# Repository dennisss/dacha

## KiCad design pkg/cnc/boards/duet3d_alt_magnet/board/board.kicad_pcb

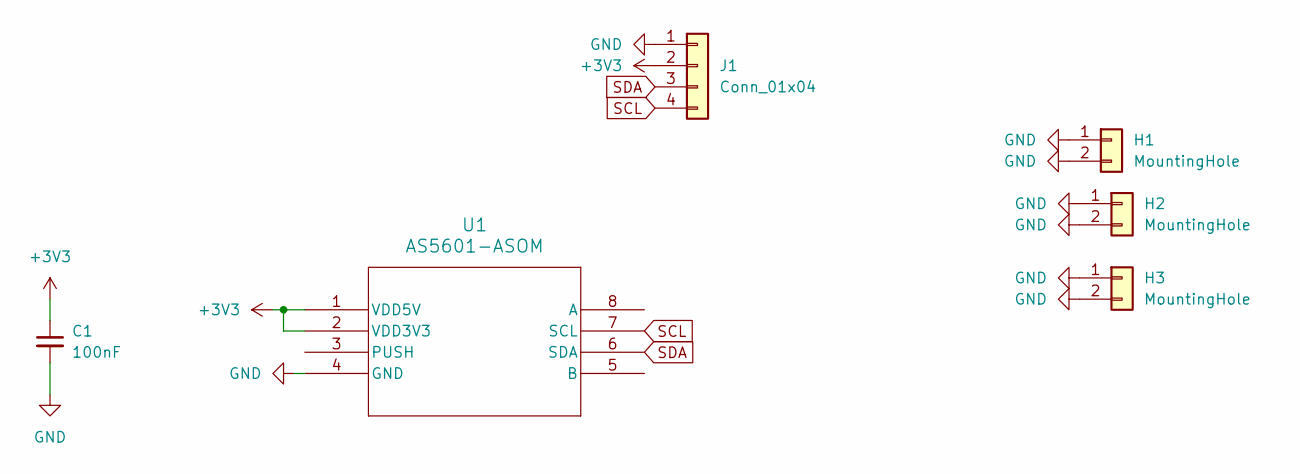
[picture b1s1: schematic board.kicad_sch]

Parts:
C1: 100nF; C_0805_2012Metric_Pad1.18x1.45mm_HandSolder
H1, H2, H3: MountingHole; M2-5-NPTH
J1: Conn_01x04; JST_SH_SM04B-SRSS-TB_1x04-1MP_P1.00mm_Horizontal
U1: AS5601-ASOM; SOIC8_AMS-M

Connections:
+3V3: C1.1, J1.2, U1.1 (VDD5V), U1.2 (VDD3V3)
GND: C1.2, H1.1, H1.2, H2.1, H2.2, H3.1, H3.2, J1.1, U1.4 (GND)
SCL: J1.4, U1.7 (SCL)
SDA: J1.3, U1.6 (SDA)

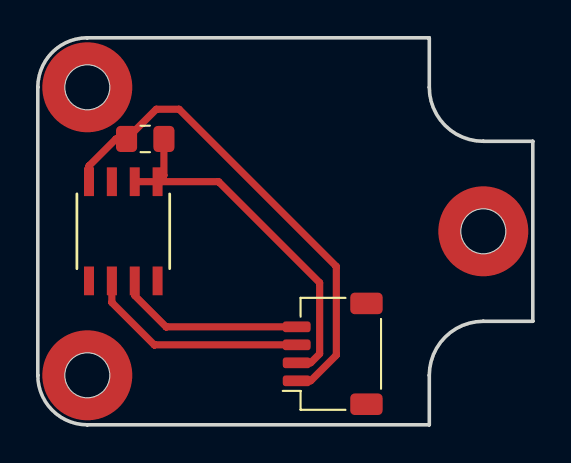
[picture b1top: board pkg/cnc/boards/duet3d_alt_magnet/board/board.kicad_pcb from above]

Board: 2 copper layers, 27.5 x 21.5 mm, 6 parts (0 on the bottom side), 4 nets.

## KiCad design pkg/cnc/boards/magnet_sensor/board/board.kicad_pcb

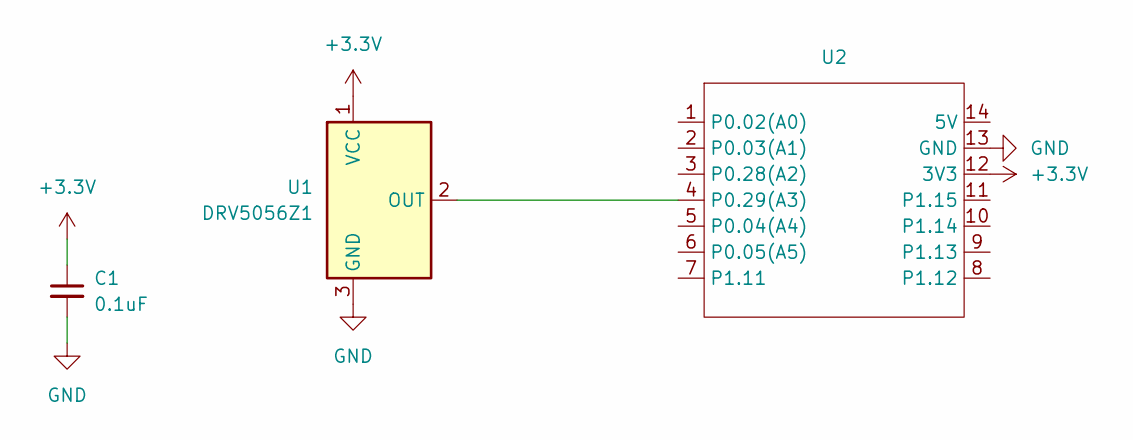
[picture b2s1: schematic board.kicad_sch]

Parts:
C1: 0.1uF; C_0805_2012Metric_Pad1.18x1.45mm_HandSolder
U1: DRV5056Z1; SOT-23
U2: XIAO_NRF52840

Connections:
+3.3V: C1.1, U1.1 (VCC), U2.12 (3V3)
GND: C1.2, U1.3 (GND), U2.13 (GND)
unnamed: U1.2 (OUT), U2.4 (P0.29(A3))

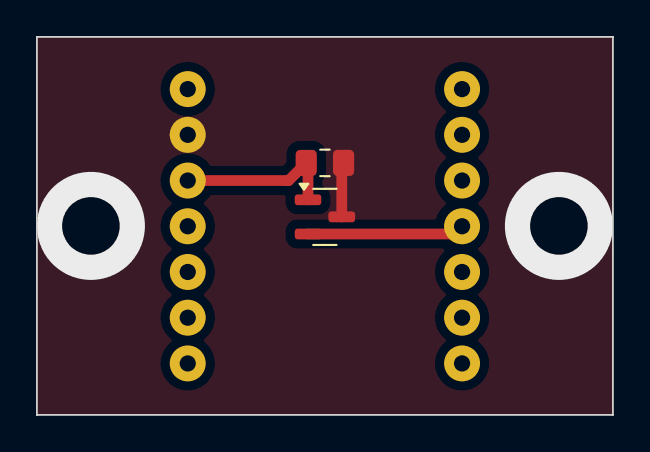
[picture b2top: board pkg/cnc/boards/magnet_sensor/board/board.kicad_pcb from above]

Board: 2 copper layers, 32.0 x 21.0 mm, 3 parts (1 on the bottom side), 3 nets.

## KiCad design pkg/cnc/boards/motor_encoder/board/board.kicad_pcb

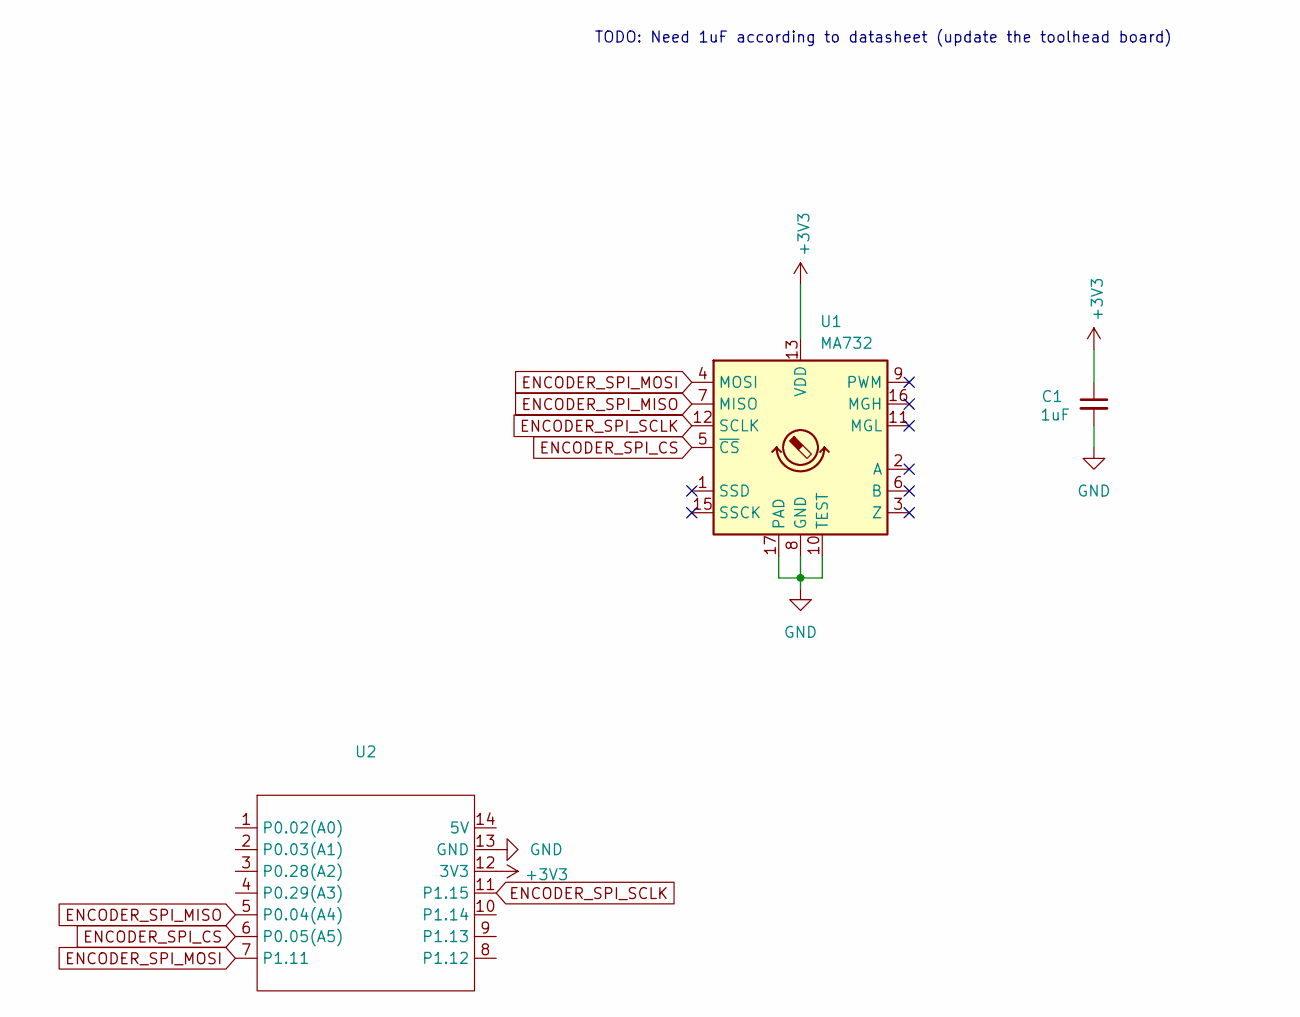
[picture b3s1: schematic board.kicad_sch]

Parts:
C1: 1uF; C_0603_1608Metric_Pad1.08x0.95mm_HandSolder
U1: MA732; QFN-16-1EP_3x3mm_P0.5mm_EP1.75x1.75mm
U2: XIAO_NRF52840

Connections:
+3V3: C1.1, U1.13 (VDD), U2.12 (3V3)
ENCODER_SPI_CS: U1.5 (~CS), U2.6 (P0.05(A5))
ENCODER_SPI_MISO: U1.7 (MISO), U2.5 (P0.04(A4))
ENCODER_SPI_MOSI: U1.4 (MOSI), U2.7 (P1.11)
ENCODER_SPI_SCLK: U1.12 (SCLK), U2.11 (P1.15)
GND: C1.2, U1.8 (GND), U1.10 (TEST), U1.17 (PAD), U2.13 (GND)

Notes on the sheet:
TODO: Need 1uF according to datasheet (update the toolhead board)

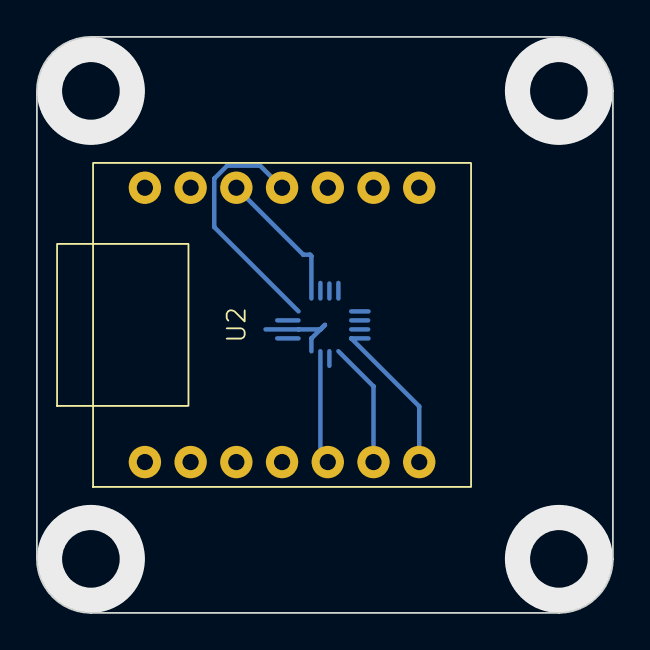
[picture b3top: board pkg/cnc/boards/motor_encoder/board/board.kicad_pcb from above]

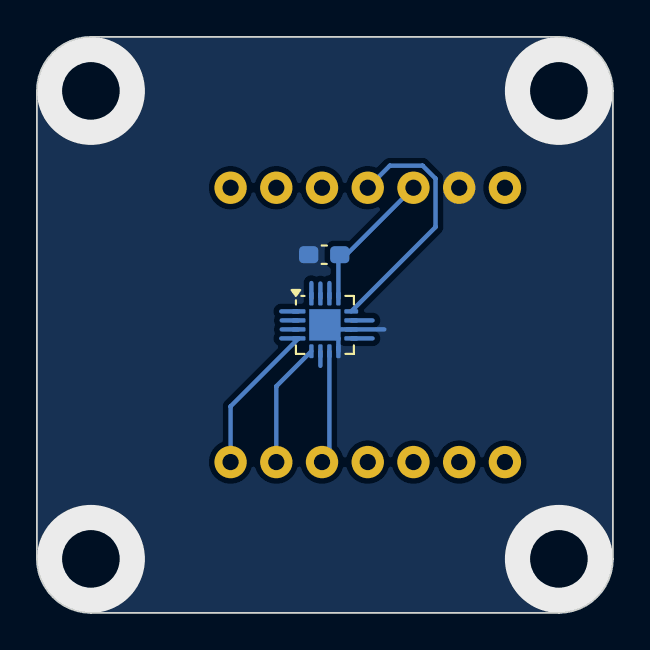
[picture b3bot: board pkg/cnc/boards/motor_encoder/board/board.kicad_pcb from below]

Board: 2 copper layers, 32.0 x 32.0 mm, 3 parts (2 on the bottom side), 6 nets.

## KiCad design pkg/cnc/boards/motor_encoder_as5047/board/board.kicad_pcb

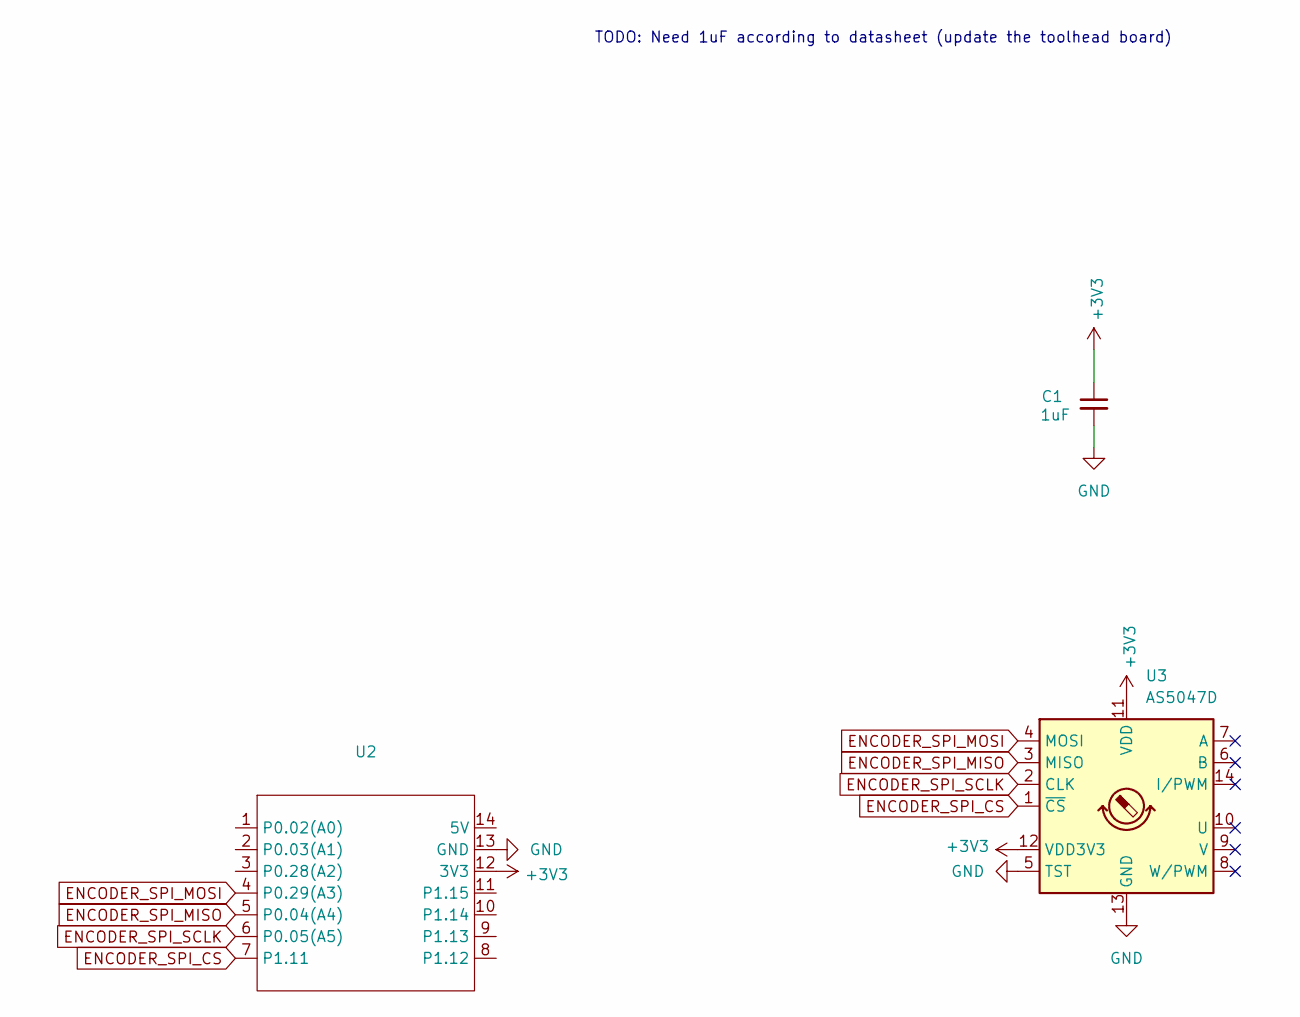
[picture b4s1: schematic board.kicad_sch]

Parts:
C1: 1uF; C_0603_1608Metric_Pad1.08x0.95mm_HandSolder
U2: XIAO_NRF52840
U3: AS5047D; TSSOP-14_4.4x5mm_P0.65mm

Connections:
+3V3: C1.1, U2.12 (3V3), U3.11 (VDD), U3.12 (VDD3V3)
ENCODER_SPI_CS: U2.7 (P1.11), U3.1 (~CS)
ENCODER_SPI_MISO: U2.5 (P0.04(A4)), U3.3 (MISO)
ENCODER_SPI_MOSI: U2.4 (P0.29(A3)), U3.4 (MOSI)
ENCODER_SPI_SCLK: U2.6 (P0.05(A5)), U3.2 (CLK)
GND: C1.2, U2.13 (GND), U3.5 (TST), U3.13 (GND)

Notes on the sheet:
TODO: Need 1uF according to datasheet (update the toolhead board)

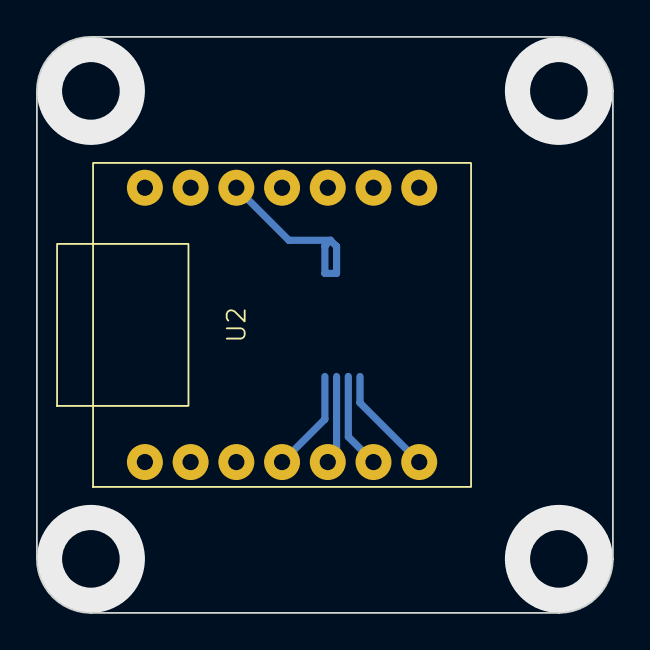
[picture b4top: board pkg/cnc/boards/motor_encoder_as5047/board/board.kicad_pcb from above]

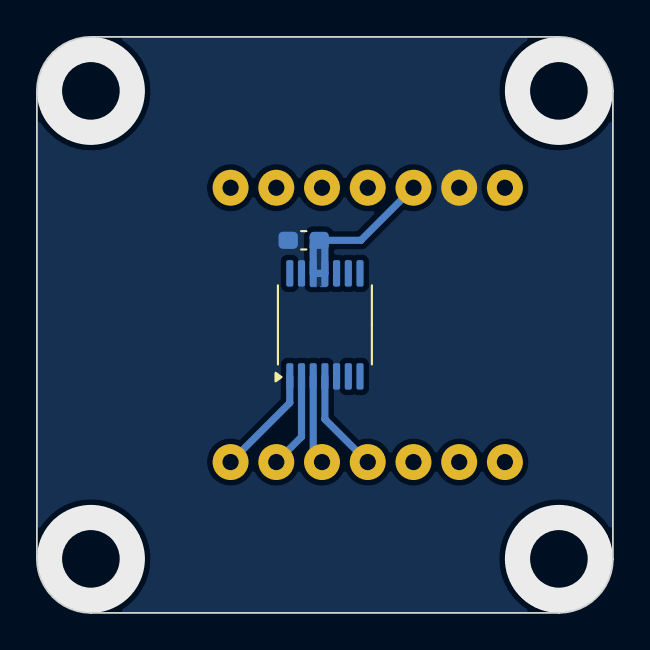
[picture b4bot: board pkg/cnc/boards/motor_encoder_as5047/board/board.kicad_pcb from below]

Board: 2 copper layers, 32.0 x 32.0 mm, 3 parts (2 on the bottom side), 6 nets.

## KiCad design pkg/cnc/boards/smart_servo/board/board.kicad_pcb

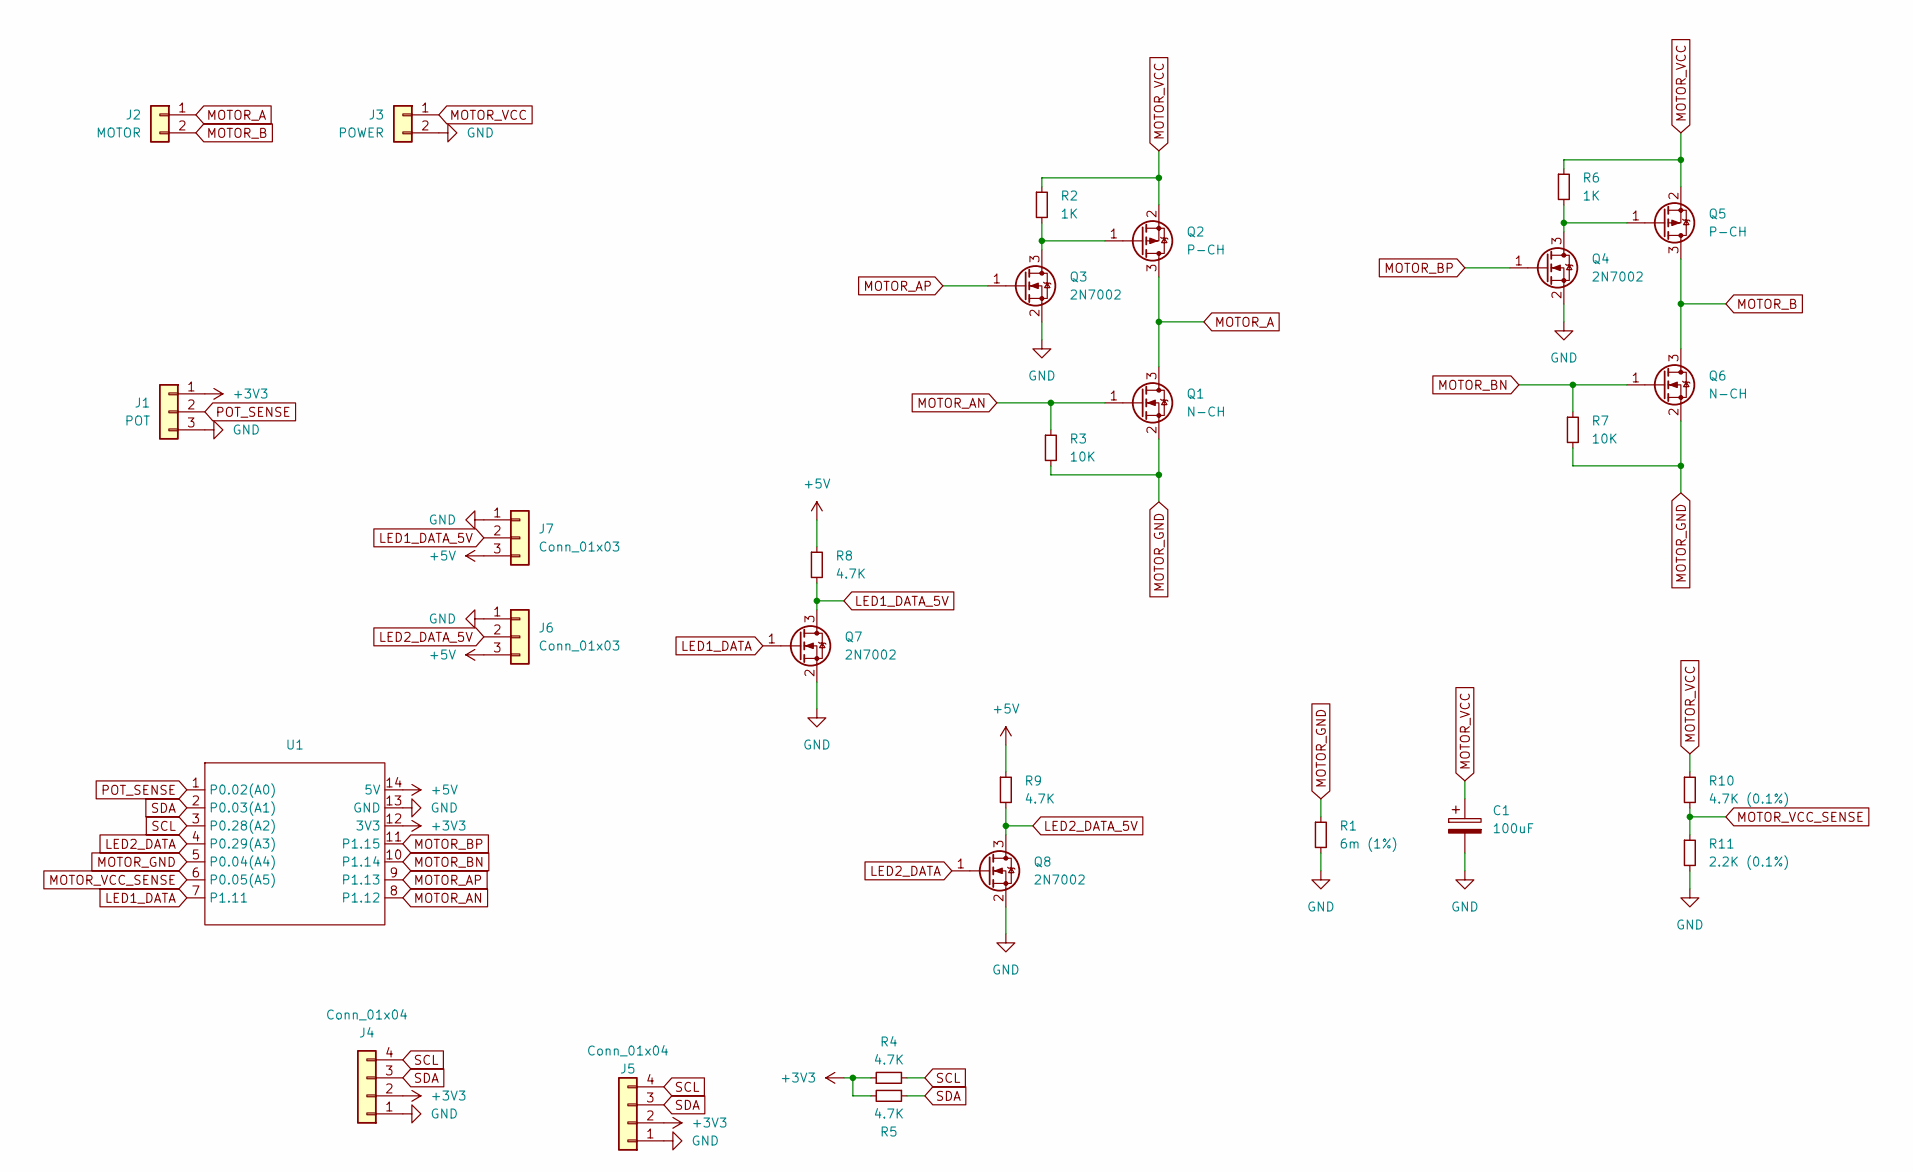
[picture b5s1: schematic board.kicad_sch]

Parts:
C1: 100uF; CP_Elec_6.3x7.7
J1: POT; JST_PH_S3B-PH-K_1x03_P2.00mm_Horizontal
J2: MOTOR; JST_XH_S2B-XH-A_1x02_P2.50mm_Horizontal
J3: POWER; Molex_Micro-Fit_3.0_43650-0210_1x02-1MP_P3.00mm_Horizontal
J4, J5: Conn_01x04; JST_SH_SM04B-SRSS-TB_1x04-1MP_P1.00mm_Horizontal
J6, J7: Conn_01x03; JST_PH_S3B-PH-K_1x03_P2.00mm_Horizontal
Q1, Q6: N-CH; SOT-23
Q2, Q5: P-CH; SOT-23
Q3, Q4, Q7, Q8: 2N7002; SOT-23
R1: 6m (1%); R_0805_2012Metric_Pad1.20x1.40mm_HandSolder
R2, R6: 1K; R_0603_1608Metric_Pad0.98x0.95mm_HandSolder
R3, R7: 10K; R_0603_1608Metric_Pad0.98x0.95mm_HandSolder
R4, R5, R8, R9: 4.7K; R_0603_1608Metric_Pad0.98x0.95mm_HandSolder
R10: 4.7K (0.1%); R_0603_1608Metric_Pad0.98x0.95mm_HandSolder
R11: 2.2K (0.1%); R_0603_1608Metric_Pad0.98x0.95mm_HandSolder
U1: XIAO_NRF52840

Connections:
+3V3: J1.1, J4.2, J5.2, R4.1, R5.2, U1.12 (3V3)
+5V: J6.3, J7.3, R8.1, R9.1, U1.14 (5V)
GND: C1.2, J1.3, J3.2, J3.MP, J4.1, J5.1, J6.1, J7.1, Q3.2 (S), Q4.2 (S), Q7.2 (S), Q8.2 (S), R1.2, R11.2, U1.13 (GND)
LED1_DATA: Q7.1 (G), U1.7 (P1.11)
LED1_DATA_5V: J7.2, Q7.3 (D), R8.2
LED2_DATA: Q8.1 (G), U1.4 (P0.29(A3))
LED2_DATA_5V: J6.2, Q8.3 (D), R9.2
MOTOR_A: J2.1, Q1.3 (D), Q2.3 (D)
MOTOR_AN: Q1.1 (G), R3.1, U1.8 (P1.12)
MOTOR_AP: Q3.1 (G), U1.9 (P1.13)
MOTOR_B: J2.2, Q5.3 (D), Q6.3 (D)
MOTOR_BN: Q6.1 (G), R7.1, U1.10 (P1.14)
MOTOR_BP: Q4.1 (G), U1.11 (P1.15)
MOTOR_GND: Q1.2 (S), Q6.2 (S), R1.1, R3.2, R7.2, U1.5 (P0.04(A4))
MOTOR_VCC: C1.1, J3.1, Q2.2 (S), Q5.2 (S), R2.1, R6.1, R10.1
MOTOR_VCC_SENSE: R10.2, R11.1, U1.6 (P0.05(A5))
unnamed: Q2.1 (G), Q3.3 (D), R2.2
unnamed: Q4.3 (D), Q5.1 (G), R6.2
POT_SENSE: J1.2, U1.1 (P0.02(A0))
SCL: J4.4, J5.4, R4.2, U1.3 (P0.28(A2))
SDA: J4.3, J5.3, R5.1, U1.2 (P0.03(A1))

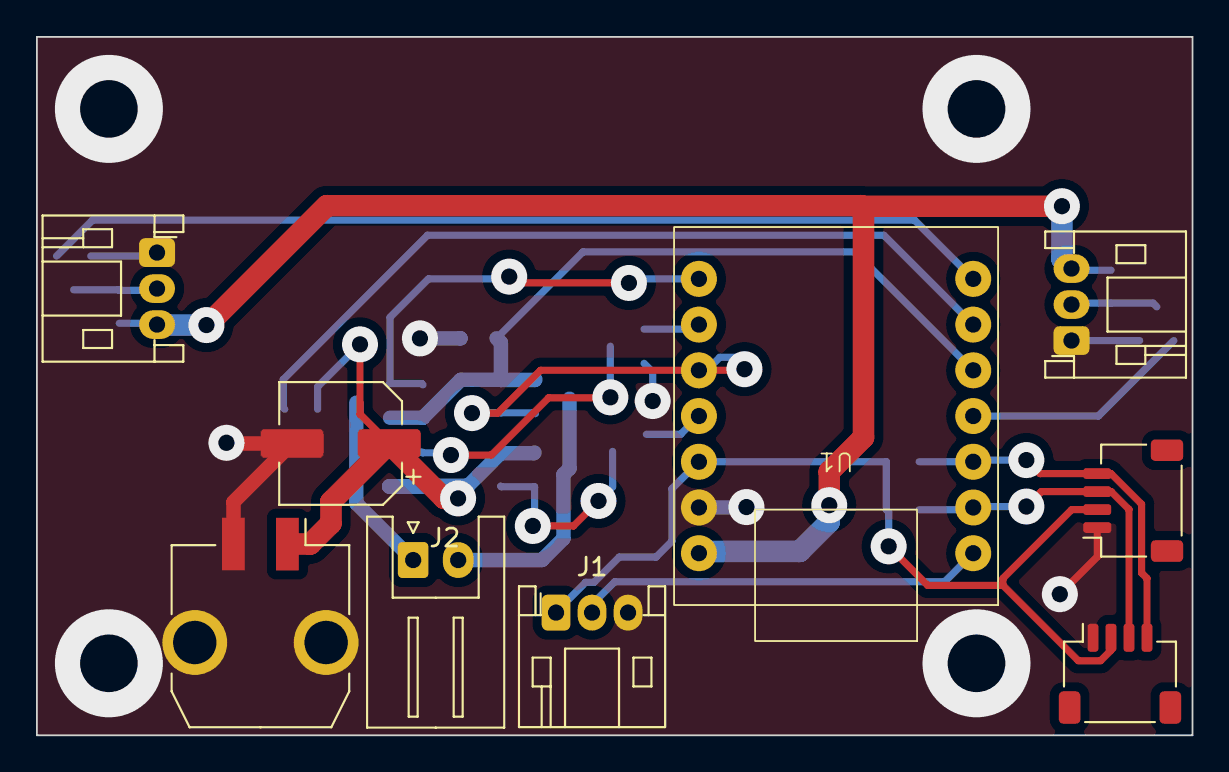
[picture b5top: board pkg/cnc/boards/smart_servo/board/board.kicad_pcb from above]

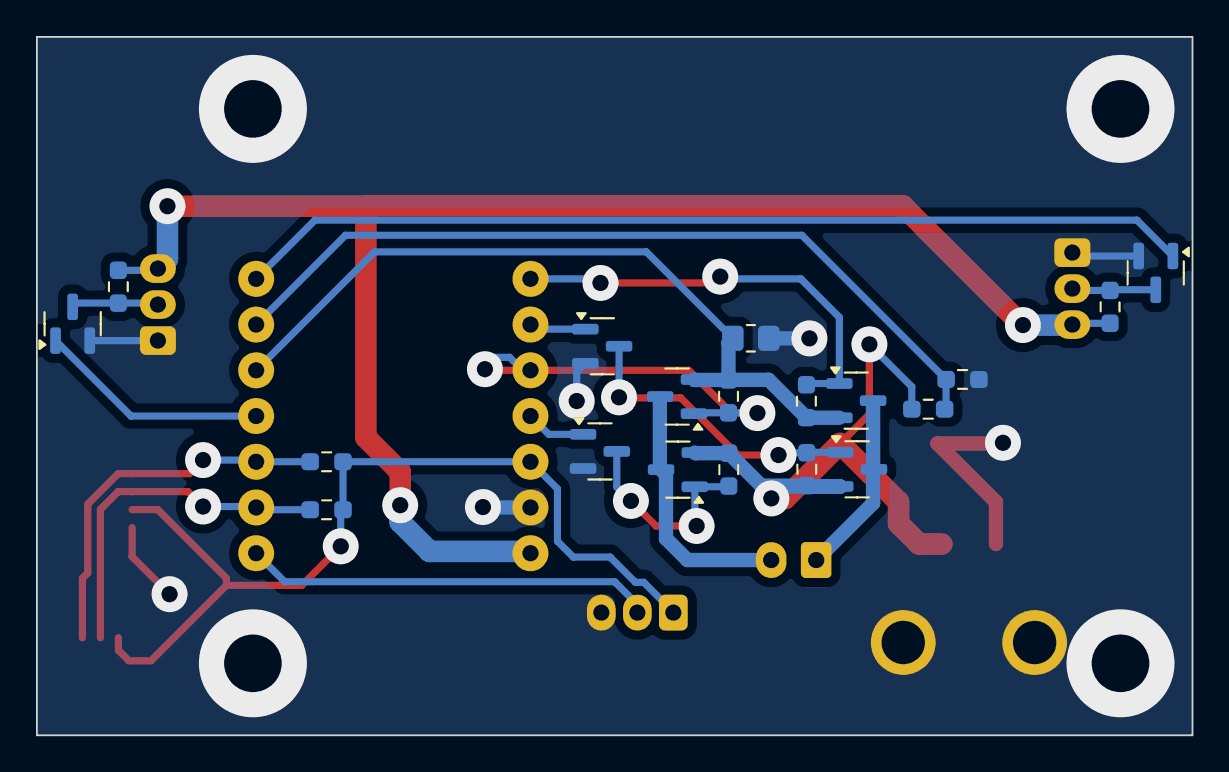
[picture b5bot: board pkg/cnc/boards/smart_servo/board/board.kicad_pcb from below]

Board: 2 copper layers, 64.2 x 38.8 mm, 28 parts (19 on the bottom side), 21 nets.

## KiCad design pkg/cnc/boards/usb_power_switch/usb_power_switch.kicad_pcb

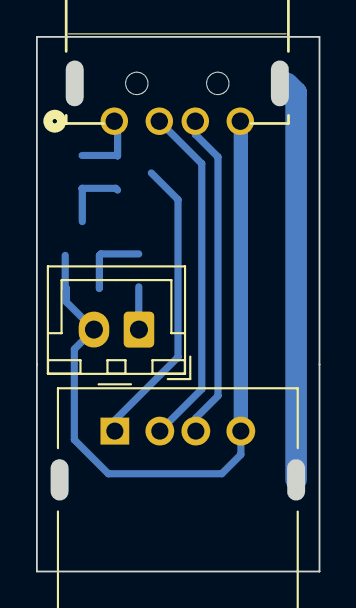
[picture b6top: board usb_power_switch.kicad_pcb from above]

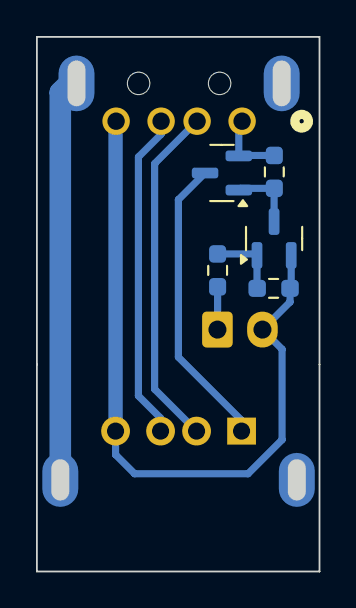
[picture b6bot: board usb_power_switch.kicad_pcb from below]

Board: 2 copper layers, 15.7 x 29.7 mm, 8 parts (5 on the bottom side), 9 nets.

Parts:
J1: USB_A_FEMALE; USB_A_Molex_67643_Horizontal
J2: USB_A_MALE; CONN_480370001_MOL
J3: Conn_01x02; JST_XH_B2B-XH-A_1x02_P2.50mm_Vertical
Q1: DMG2301L; SOT-23
Q2: 2N7002; SOT-23
R1, R2: 100K; R_0603_1608Metric_Pad0.98x0.95mm_HandSolder
R3: 50K; R_0603_1608Metric_Pad0.98x0.95mm_HandSolder

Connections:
5V_OUT: J1.1 (VBUS), Q1.3 (D)
+5V: J2.1 (VBUS), Q1.2 (S), R1.1
D+: J1.3 (D+), J2.3 (D+)
D-: J1.2 (D-), J2.2 (D-)
GND: J1.4 (GND), J2.4 (GND), J3.2, Q2.2 (S), R2.2
unnamed: J3.1, R3.1
unnamed: Q1.1 (G), Q2.3 (D), R1.2
unnamed: Q2.1 (G), R2.1, R3.2
SHIELD: J1.5 (Shield), J2.5 (Shield)
